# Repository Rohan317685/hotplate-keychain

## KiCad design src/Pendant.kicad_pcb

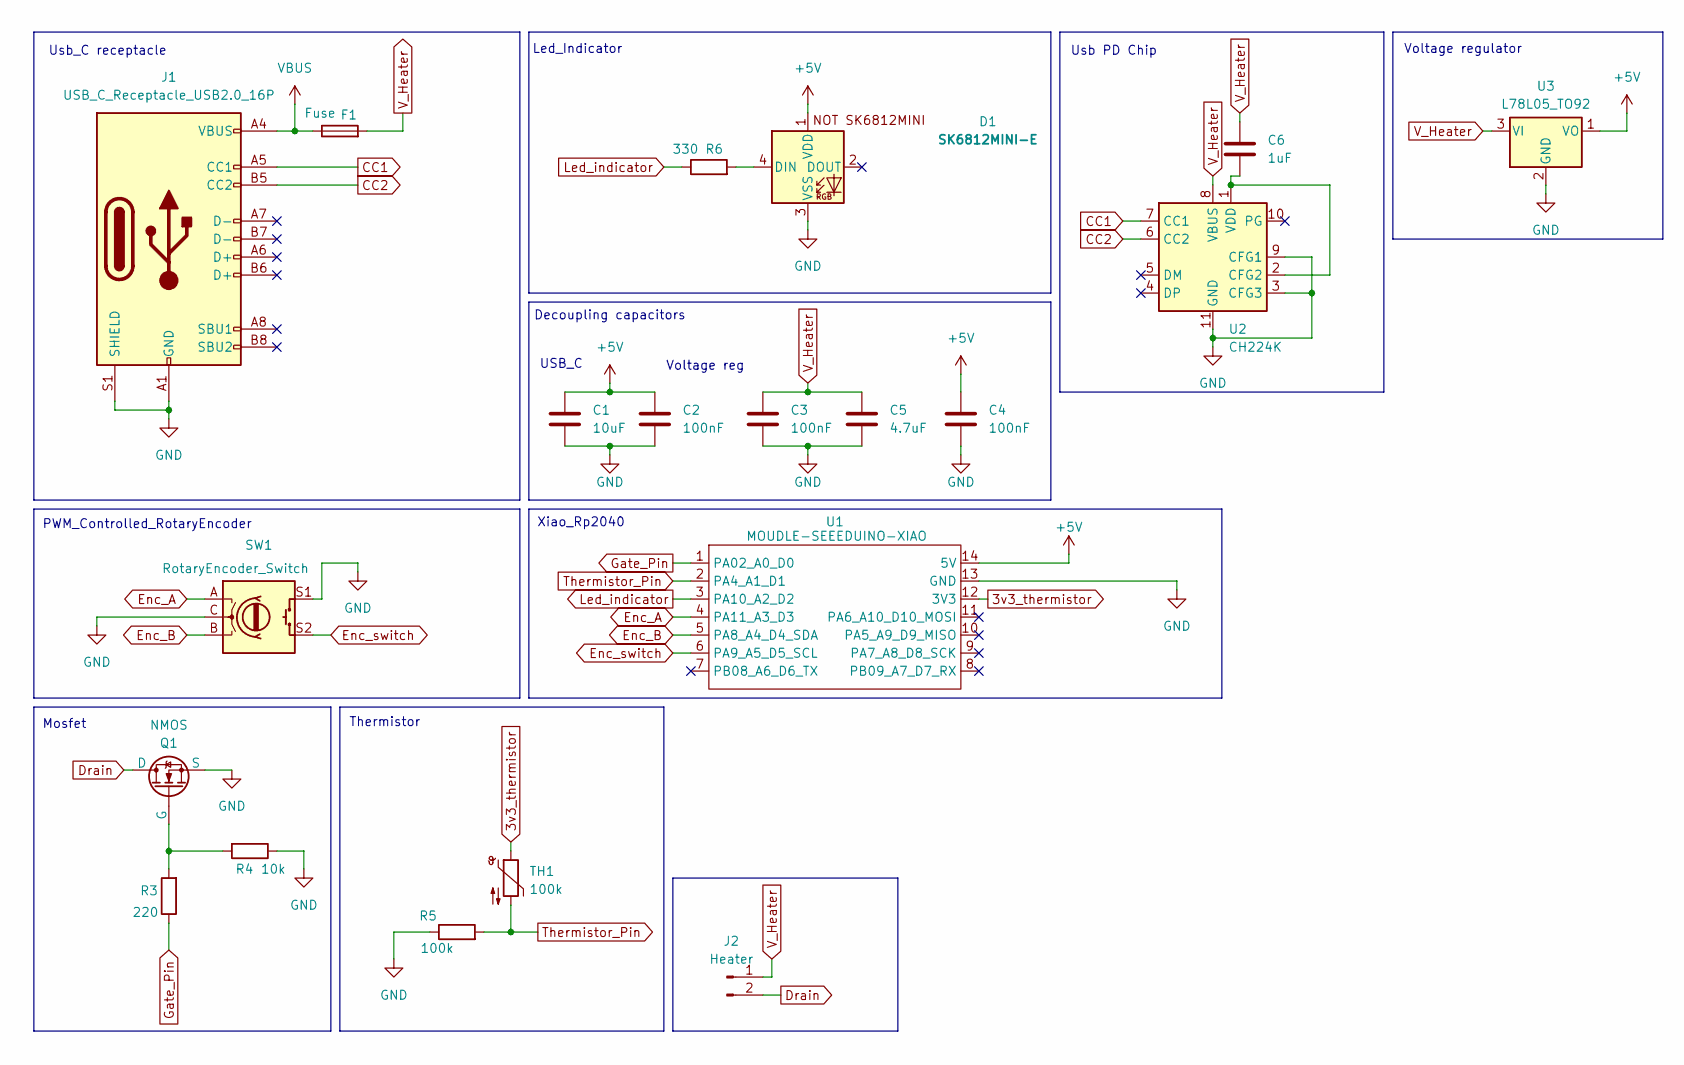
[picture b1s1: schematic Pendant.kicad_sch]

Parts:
C1: 10uF; CP_Radial_D5.0mm_P2.00mm
C2, C3, C4: 100nF; C_Disc_D3.0mm_W2.0mm_P2.50mm
C5: 4.7uF; CP_Radial_D5.0mm_P2.00mm
C6: 1uF; C_Disc_D4.3mm_W1.9mm_P5.00mm
D1: SK6812MINI-E; SK6812MINI-E_fixed
F1: Fuse; Fuse_Littelfuse_372_D8.50mm
J1: USB_C_Receptacle_USB2.0_16P; USB_C_Receptacle_HRO_TYPE-C-31-M-12
J2: Heater; PinHeader_1x02_P2.54mm_Vertical
Q1: NMOS; TO-220-3_Vertical
R3: 220; R_Axial_DIN0207_L6.3mm_D2.5mm_P7.62mm_Horizontal
R4: 10k; R_Axial_DIN0207_L6.3mm_D2.5mm_P7.62mm_Horizontal
R5: 100k; R_Axial_DIN0207_L6.3mm_D2.5mm_P7.62mm_Horizontal
R6: 330; R_Axial_DIN0207_L6.3mm_D2.5mm_P7.62mm_Horizontal
SW1: RotaryEncoder_Switch; RotaryEncoder_Alps_EC11E-Switch_Vertical_H20mm_MountingHoles
TH1: 100k; R_0805_2012Metric
U1: MOUDLE-SEEEDUINO-XIAO; XIAO-Generic-Hybrid-14P-2.54-21X17.8MM
U2: CH224K; SSOP-10-1EP_3.9x4.9mm_P1mm_EP2.1x3.3mm
U3: L78L05_TO92; TO-92_Inline

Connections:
3v3_thermistor: TH1.1, U1.12 (3V3)
+5V: C1.1, C2.1, C4.1, D1.1 (VDD), U1.14 (5V), U3.1 (VO)
CC1: J1.A5 (CC1), U2.7 (CC1)
CC2: J1.B5 (CC2), U2.6 (CC2)
Drain: J2.2, Q1.1 (D)
Enc_A: SW1.A, U1.4 (PA11_A3_D3)
Enc_B: SW1.B, U1.5 (PA8_A4_D4_SDA)
Enc_switch: SW1.S2, U1.6 (PA9_A5_D5_SCL)
GND: C1.2, C2.2, C3.2, C4.2, C5.2, D1.3 (VSS), J1.A1 (GND), J1.A12 (GND), J1.B1 (GND), J1.B12 (GND), J1.S1 (SHIELD), Q1.3 (S), R4.1, R5.1, SW1.C, SW1.S1, U1.13 (GND), U2.3 (CFG3), U2.9 (CFG1), U2.11 (GND), U3.2 (GND)
Gate_Pin: R3.1, U1.1 (PA02_A0_D0)
Led_indicator: R6.1, U1.3 (PA10_A2_D2)
unnamed: D1.4 (DIN), R6.2
unnamed: Q1.2 (G), R3.2, R4.2
unnamed: C6.2, U2.1 (VDD), U2.2 (CFG2)
Thermistor_Pin: R5.2, TH1.2, U1.2 (PA4_A1_D1)
VBUS: F1.1, J1.A4 (VBUS), J1.A9 (VBUS), J1.B4 (VBUS), J1.B9 (VBUS)
V_Heater: C3.1, C5.1, C6.1, F1.2, J2.1, U2.8 (VBUS), U3.3 (VI)

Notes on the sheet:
Thermistor
USB_C
Mosfet
Voltage regulator
Decoupling capacitors
Usb_C receptacle
Usb PD Chip
Led_Indicator
Xiao_Rp2040
PWM_Controlled_RotaryEncoder
Voltage reg

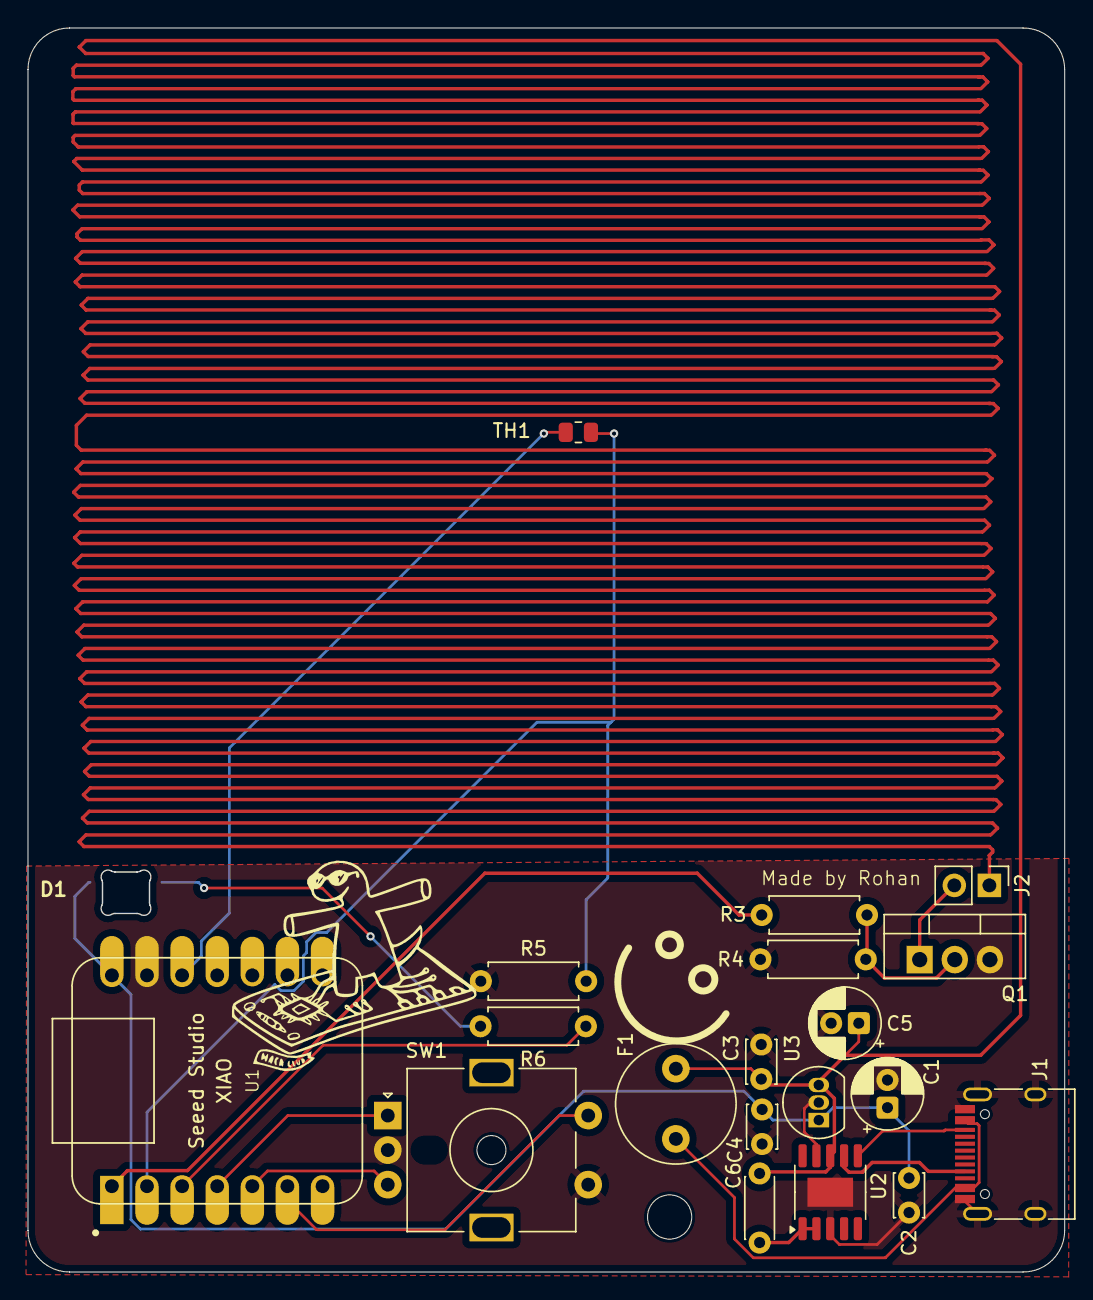
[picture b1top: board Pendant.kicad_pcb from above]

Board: 2 copper layers, 74.9 x 89.9 mm, 20 parts (0 on the bottom side), 17 nets.

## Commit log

2026-06-18 not 4.2 hours 3.2 :sob: Im never journalling at 3 am again
